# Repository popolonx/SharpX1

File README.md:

Sharp x1 related expansion boards
- CZ-8RS  RS232-serial board
- CZ-8RB One rom version (64K rom)
- CZ-VO-20PX with CPLD (vhd control board using CPLD for I/O logic)

Sharp teloper unit, CZ-8DT

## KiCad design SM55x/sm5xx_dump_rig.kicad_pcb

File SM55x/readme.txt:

SM550/1/2 (LU552xx used in Sharp VHD player) rom dump pcb with Raspberry PI pico

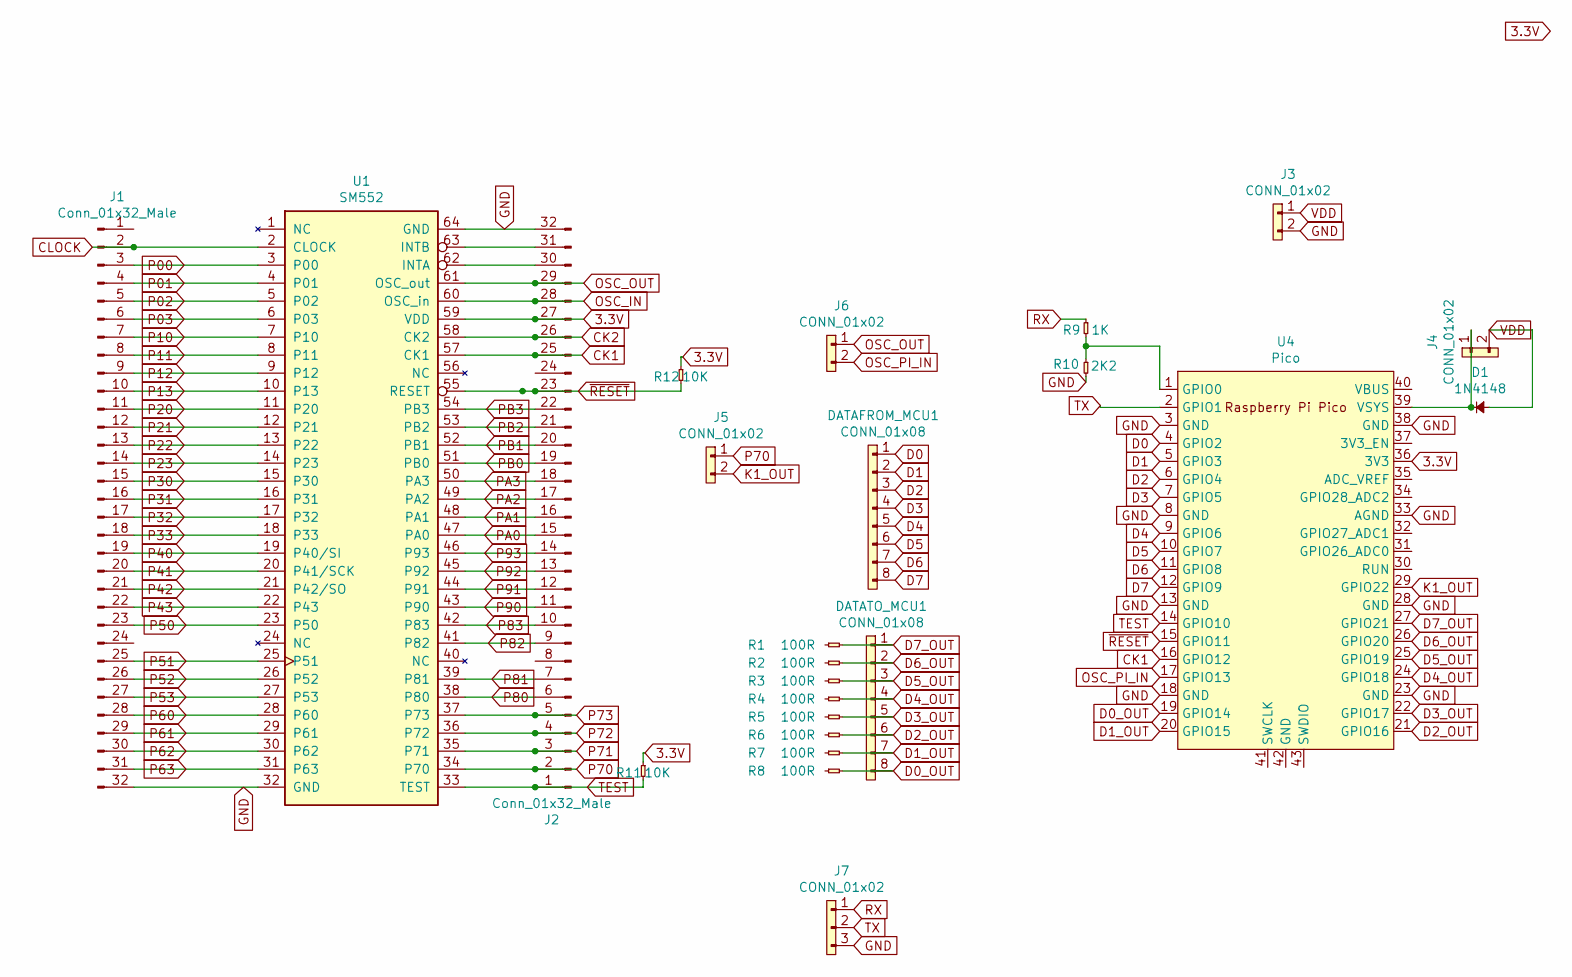
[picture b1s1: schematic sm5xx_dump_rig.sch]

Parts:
D1: 1N4148; D_DO-15_P5.08mm_Vertical_AnodeUp
DATAFROM_MCU1: CONN_01x08; PinHeader_1x08_P2.54mm_Vertical
DATATO_MCU1: CONN_01x08; PinHeader_1x08_P2.54mm_Vertical
J1, J2: Conn_01x32_Male; PinHeader_1x32_P2.54mm_Vertical
J3, J4, J5, J6: CONN_01x02; PinHeader_1x02_P2.54mm_Vertical
J7: CONN_01x02; PinHeader_1x03_P2.54mm_Vertical
R1, R2, R3, R4, R5, R6, R7, R8: 100R; R_Axial_DIN0204_L3.6mm_D1.6mm_P7.62mm_Horizontal
R9: 1K; R_Axial_DIN0204_L3.6mm_D1.6mm_P7.62mm_Horizontal
R10: 2K2; R_Axial_DIN0204_L3.6mm_D1.6mm_P7.62mm_Horizontal
R11, R12: 10K; R_Axial_DIN0204_L3.6mm_D1.6mm_P7.62mm_Horizontal
U1: SM552; DIP64_19.05mm_1.778mm
U4: Pico; RPi_Pico_THT

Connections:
3.3V: J2.27, R11.1, R12.1, U1.59 (VDD), U4.36 (3V3)
CK1: J2.25, U1.57 (CK1), U4.16 (GPIO12)
CK2: J2.26, U1.58 (CK2)
CLOCK: J1.2, U1.2 (CLOCK)
D0: DATAFROM_MCU1.1, U4.4 (GPIO2)
D0_OUT: DATATO_MCU1.8, R8.2, U4.19 (GPIO14)
D1: DATAFROM_MCU1.2, U4.5 (GPIO3)
D1_OUT: DATATO_MCU1.7, R7.2, U4.20 (GPIO15)
D2: DATAFROM_MCU1.3, U4.6 (GPIO4)
D2_OUT: DATATO_MCU1.6, R6.2, U4.21 (GPIO16)
D3: DATAFROM_MCU1.4, U4.7 (GPIO5)
D3_OUT: DATATO_MCU1.5, R5.2, U4.22 (GPIO17)
D4: DATAFROM_MCU1.5, U4.9 (GPIO6)
D4_OUT: DATATO_MCU1.4, R4.2, U4.24 (GPIO18)
D5: DATAFROM_MCU1.6, U4.10 (GPIO7)
D5_OUT: DATATO_MCU1.3, R3.2, U4.25 (GPIO19)
D6: DATAFROM_MCU1.7, U4.11 (GPIO8)
D6_OUT: DATATO_MCU1.2, R2.2, U4.26 (GPIO20)
D7: DATAFROM_MCU1.8, U4.12 (GPIO9)
D7_OUT: DATATO_MCU1.1, R1.2, U4.27 (GPIO21)
GND: J1.32, J2.32, J3.2, J7.3, R10.2, U1.32 (GND), U1.64 (GND), U4.3 (GND), U4.8 (GND), U4.13 (GND), U4.18 (GND), U4.23 (GND), U4.28 (GND), U4.33 (AGND), U4.38 (GND)
K1_OUT: J5.2, U4.29 (GPIO22)
unnamed: D1.1, J4.1, U4.39 (VSYS)
unnamed: J2.30, U1.62 (INTA)
unnamed: J2.31, U1.63 (INTB)
unnamed: R9.2, R10.1, U4.1 (GPIO0)
OSC_IN: J2.28, U1.60 (OSC_in)
OSC_OUT: J2.29, J6.1, U1.61 (OSC_out)
OSC_PI_IN: J6.2, U4.17 (GPIO13)
P00: J1.3, U1.3 (P00)
P01: J1.4, U1.4 (P01)
P02: J1.5, U1.5 (P02)
P03: J1.6, U1.6 (P03)
P10: J1.7, U1.7 (P10)
P11: J1.8, U1.8 (P11)
P12: J1.9, U1.9 (P12)
P13: J1.10, U1.10 (P13)
P20: J1.11, U1.11 (P20)
P21: J1.12, U1.12 (P21)
P22: J1.13, U1.13 (P22)
P23: J1.14, U1.14 (P23)
P30: J1.15, U1.15 (P30)
P31: J1.16, U1.16 (P31)
P32: J1.17, U1.17 (P32)
P33: J1.18, U1.18 (P33)
P40: J1.19, U1.19 (P40/SI)
P41: J1.20, U1.20 (P41/SCK)
P42: J1.21, U1.21 (P42/SO)
P43: J1.22, U1.22 (P43)
P50: J1.23, U1.23 (P50)
P51: J1.25, U1.25 (P51)
P52: J1.26, U1.26 (P52)
P53: J1.27, U1.27 (P53)
P60: J1.28, U1.28 (P60)
P61: J1.29, U1.29 (P61)
P62: J1.30, U1.30 (P62)
P63: J1.31, U1.31 (P63)
P70: J2.2, J5.1, U1.34 (P70)
P71: J2.3, U1.35 (P71)
P72: J2.4, U1.36 (P72)
P73: J2.5, U1.37 (P73)
P80: J2.6, U1.38 (P80)
P81: J2.7, U1.39 (P81)
P82: J2.9, U1.41 (P82)
P83: J2.10, U1.42 (P83)
P90: J2.11, U1.43 (P90)
P91: J2.12, U1.44 (P91)
P92: J2.13, U1.45 (P92)
P93: J2.14, U1.46 (P93)
PA0: J2.15, U1.47 (PA0)
PA1: J2.16, U1.48 (PA1)
PA2: J2.17, U1.49 (PA2)
PA3: J2.18, U1.50 (PA3)
PB0: J2.19, U1.51 (PB0)
PB1: J2.20, U1.52 (PB1)
PB2: J2.21, U1.53 (PB2)
PB3: J2.22, U1.54 (PB3)
RX: J7.1, R9.1
TEST: J2.1, R11.2, U1.33 (TEST), U4.14 (GPIO10)
TX: J7.2, U4.2 (GPIO1)
VDD: D1.2, J3.1, J4.2
~RESET~: J2.23, R12.2, U1.55 (RESET), U4.15 (GPIO11)

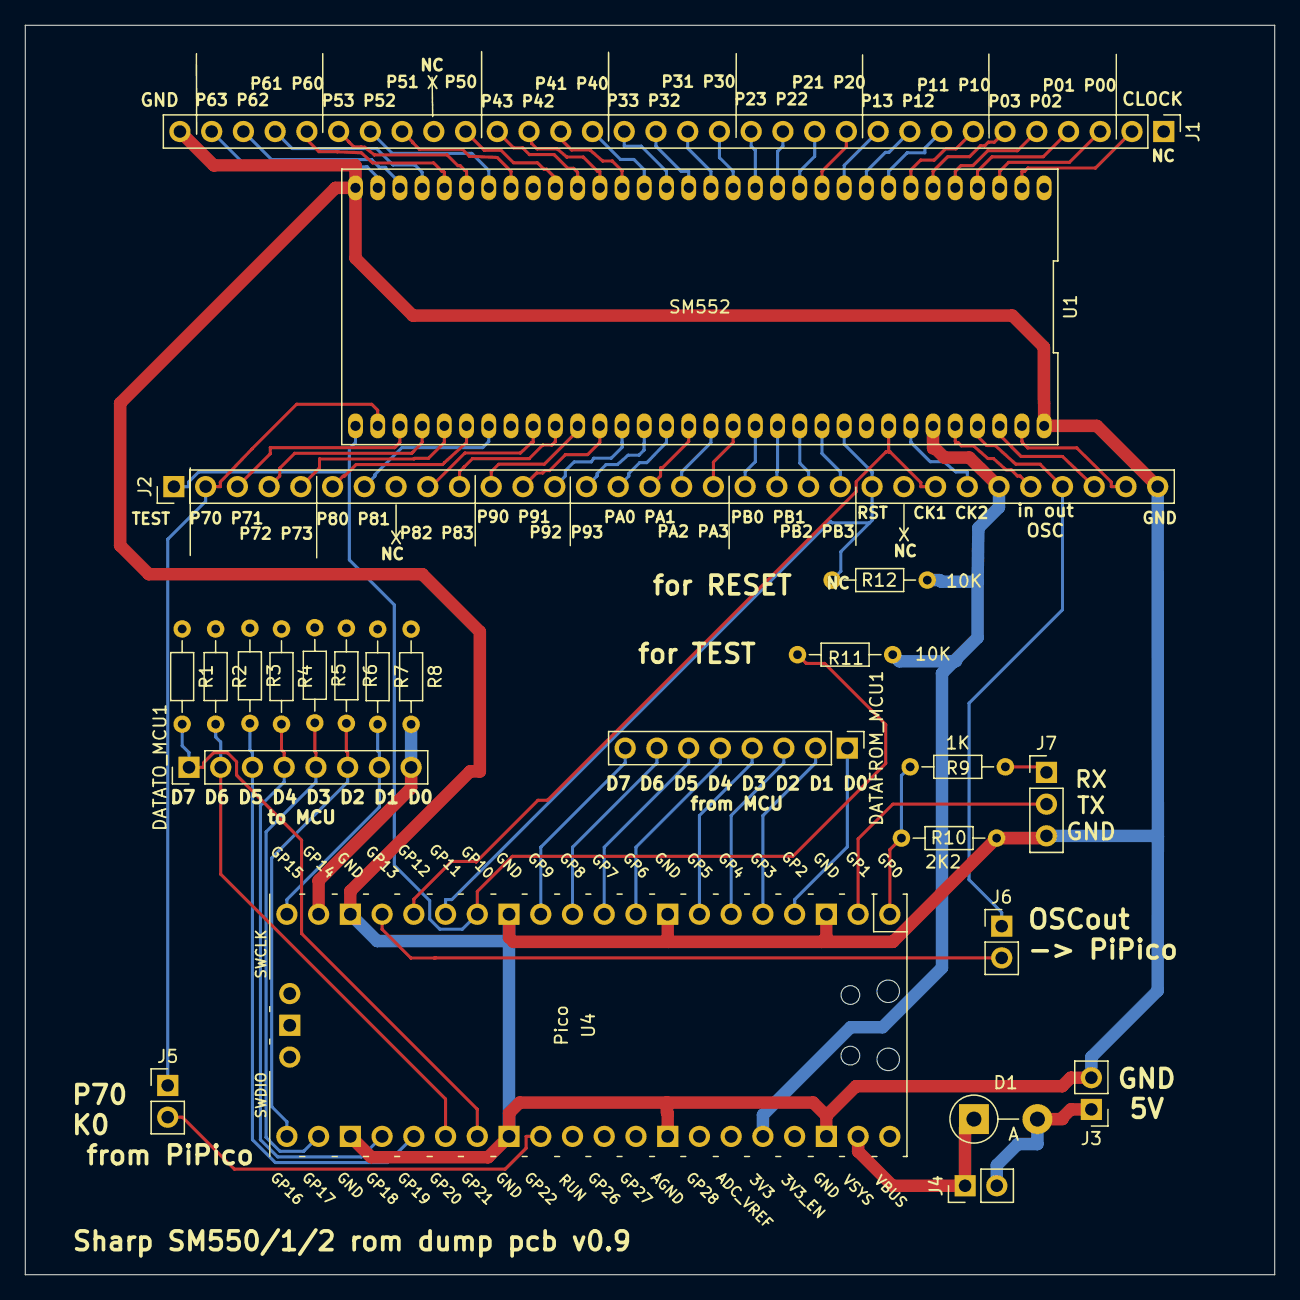
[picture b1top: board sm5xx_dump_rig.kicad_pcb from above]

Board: 2 copper layers, 100.0 x 100.0 mm, 24 parts (0 on the bottom side), 82 nets.

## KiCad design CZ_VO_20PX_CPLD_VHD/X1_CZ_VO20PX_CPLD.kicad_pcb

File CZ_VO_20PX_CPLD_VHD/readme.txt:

Sharp X1 vhd card
-implements vhd player control (VO-20PS + VO-20PC) and data decoding
-based on CZ-8RS card (RS-232) and msx vhd board (IF-C9C/D)
-CPLD version for logic side to decrease used ICs and pin count.
-DB15 connector towards VHD player (towards victor VHDpc din13, not for Sharp vhd din-8)
-needed cable connections:
--DIN13-pin3 <-> DB15-pin3
--DIN13-pin4 <-> DB15-pin4
--DIN13-pin6 <-> DB15-pin6
--DIN13-pin7 <-> DB15-pin7
--DIN13-pin8 <-> DB15-pin8
--DIN13-pin8 <-> DB15-pin9
--DIN13-pin10 <-> DB15-pin10
--DIN13-pin12 <-> DB15-pin12
--DIN13-shield <-> DB15-shield (is GND)

NOTE! Old kicad 5.1.5 used!

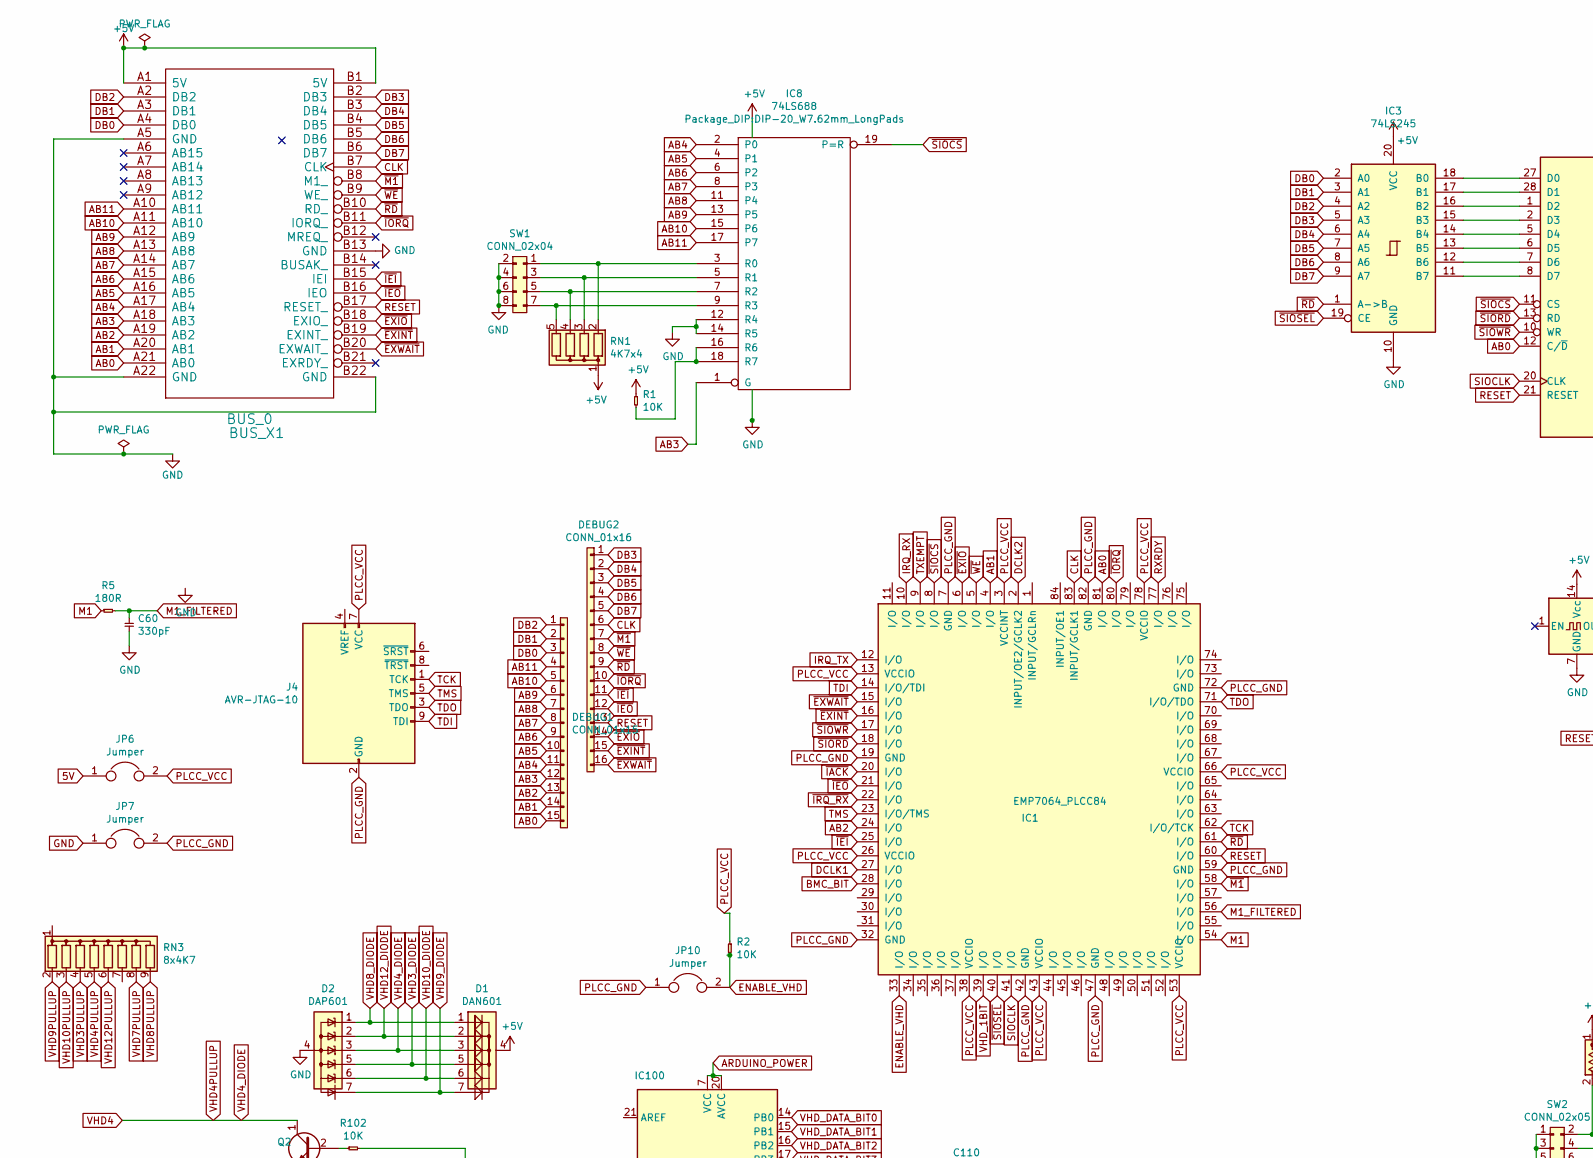
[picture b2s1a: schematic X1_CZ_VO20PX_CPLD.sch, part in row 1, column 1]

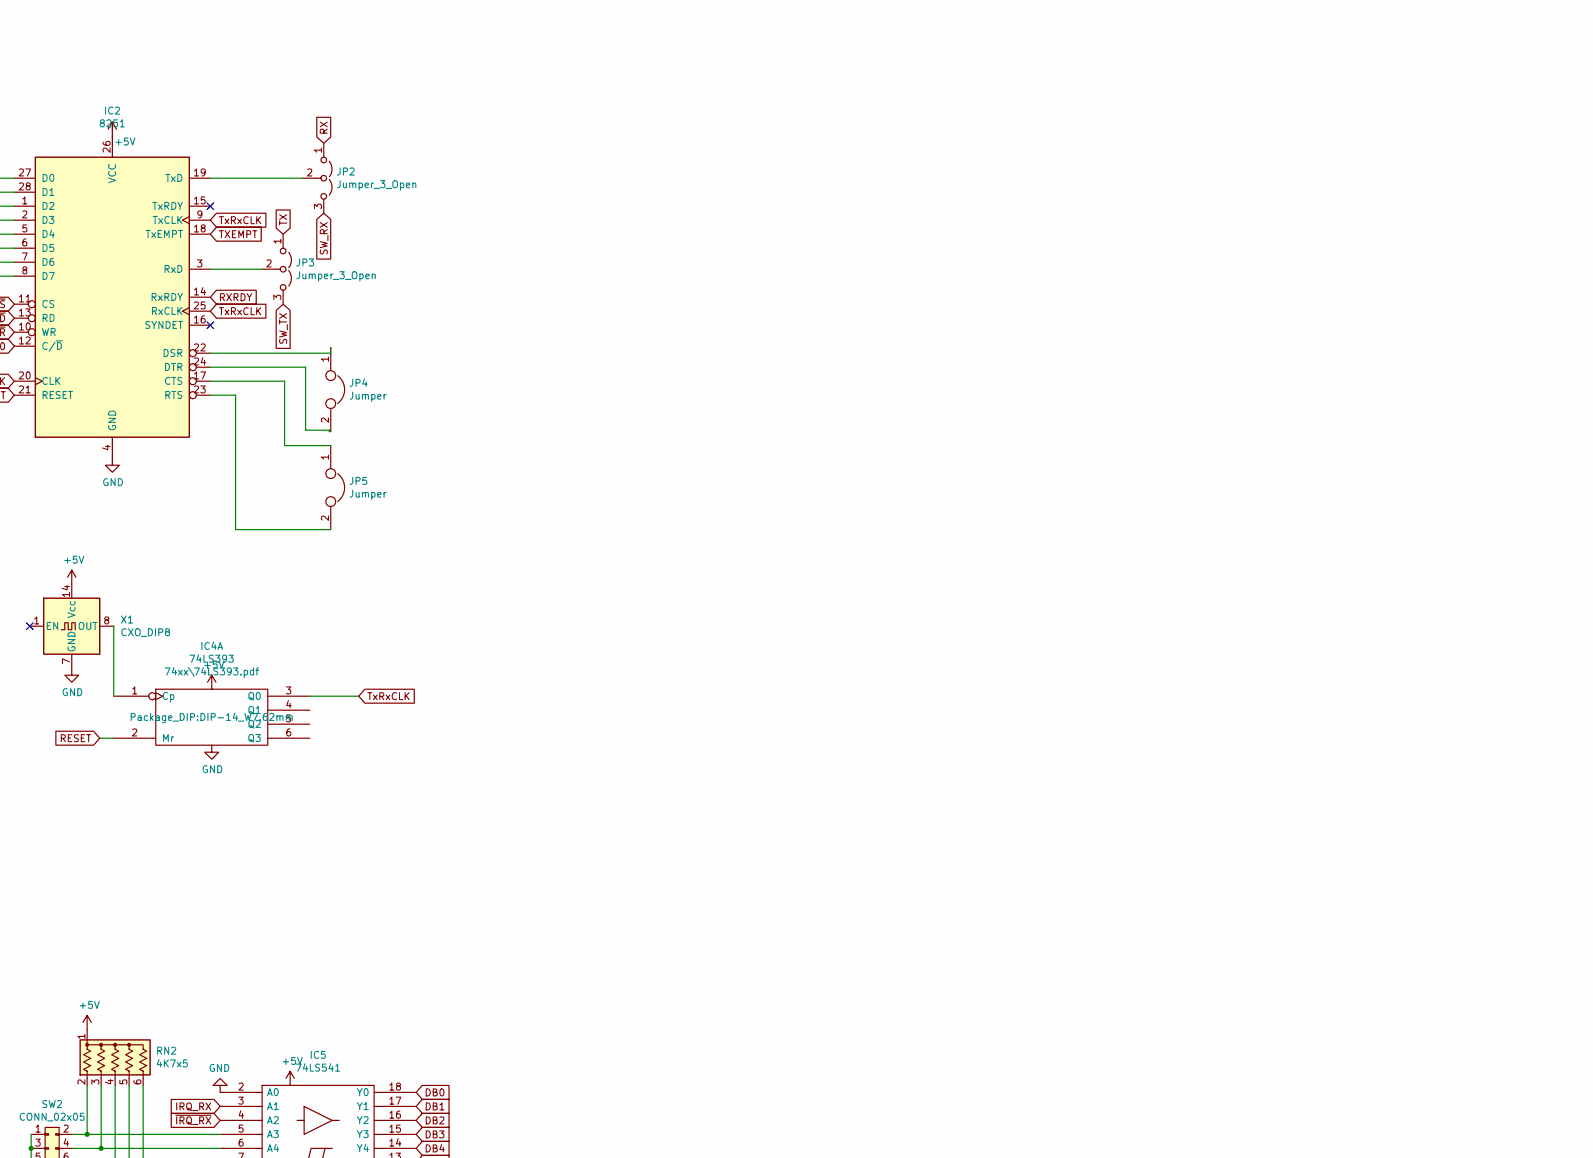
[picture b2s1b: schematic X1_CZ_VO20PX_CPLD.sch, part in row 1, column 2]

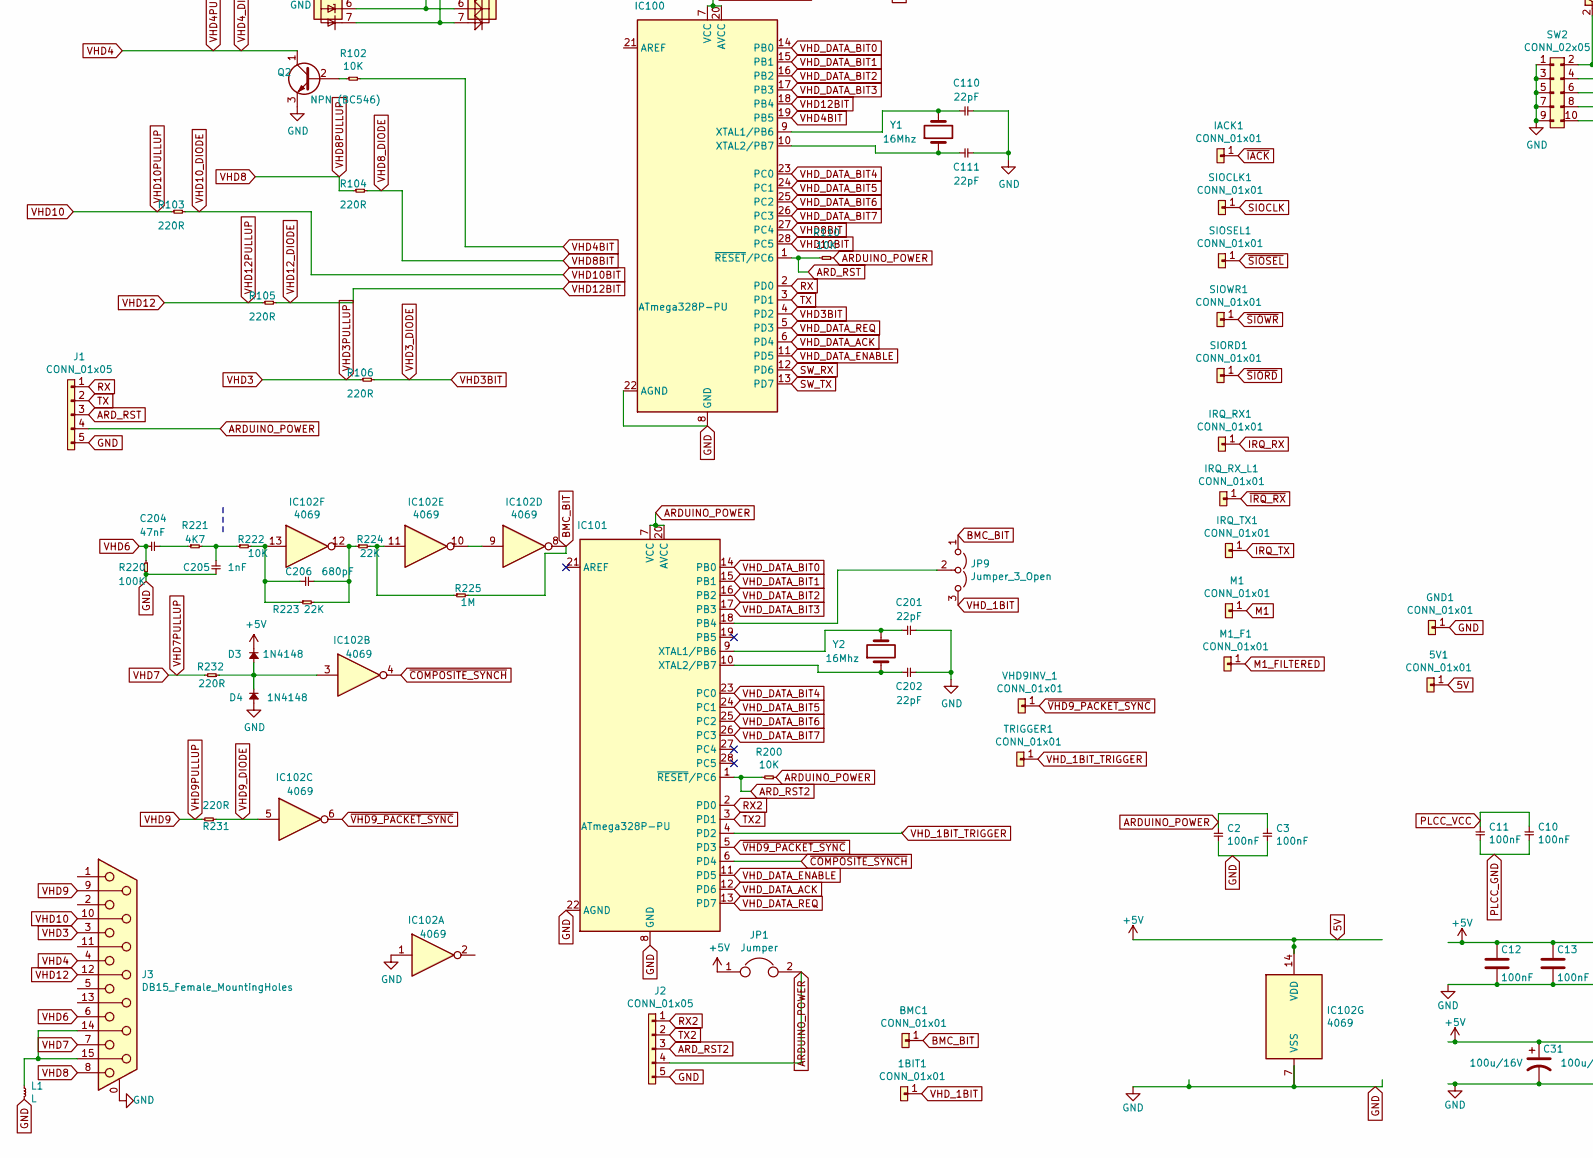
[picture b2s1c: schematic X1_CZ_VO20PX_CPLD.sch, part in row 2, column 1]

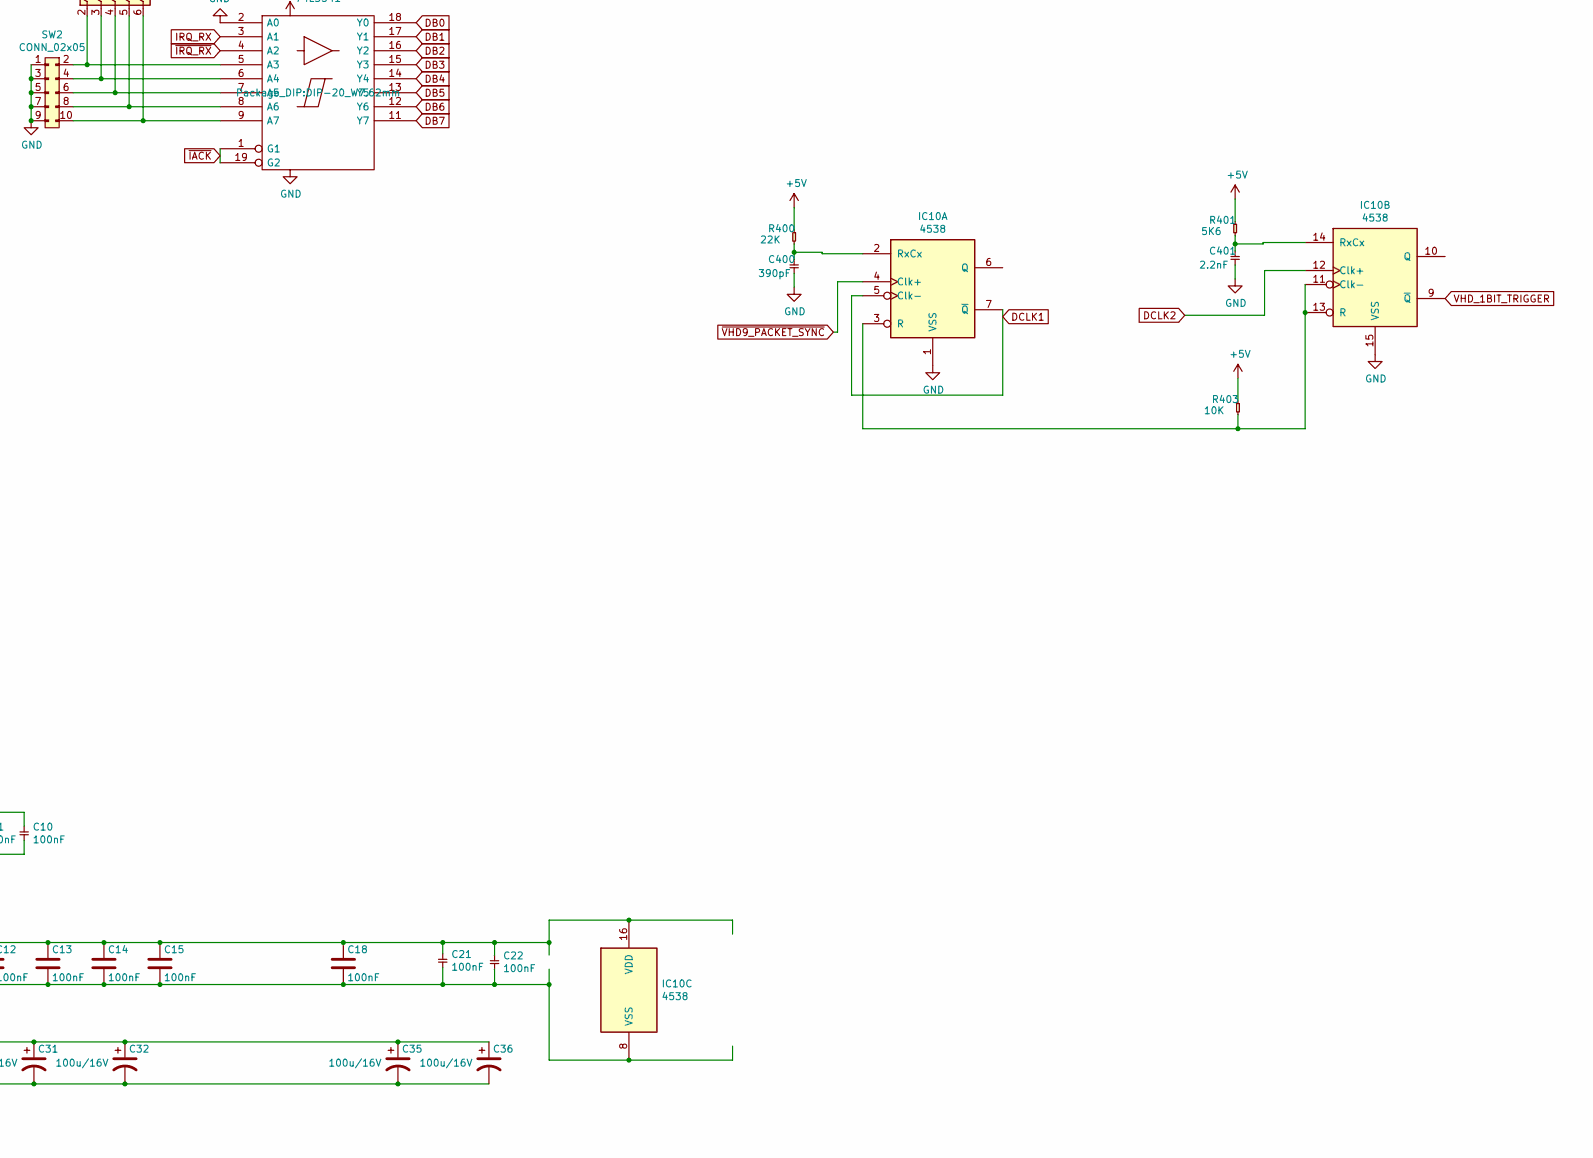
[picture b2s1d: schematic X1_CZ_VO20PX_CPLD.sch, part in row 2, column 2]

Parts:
1BIT1, 5V1: CONN_01x01; PinHeader_1x01_P2.54mm_Vertical
BMC1: CONN_01x01; PinHeader_1x01_P2.54mm_Vertical
BUS_0: BUS_X1; X1_IO
C2, C3, C10, C11, C12, C13, C14, C15, C18, C21, C22: 100nF; C_Disc_D5.0mm_W2.5mm_P5.00mm
C31, C32, C35: 100u/16V; CP_Radial_D8.0mm_P5.00mm
C36: 100u/16V; CP_Radial_D7.5mm_P2.50mm
C60: 330pF; C_Disc_D5.0mm_W2.5mm_P5.00mm
C110, C111, C201, C202: 22pF; C_Disc_D4.3mm_W1.9mm_P5.00mm
C204: 47nF; C_Disc_D5.0mm_W2.5mm_P5.00mm
C205: 1nF; C_Disc_D5.0mm_W2.5mm_P5.00mm
C206: 680pF; C_Disc_D5.0mm_W2.5mm_P5.00mm
C400: 390pF; C_Disc_D5.0mm_W2.5mm_P5.00mm
C401: 2.2nF; C_Disc_D5.0mm_W2.5mm_P5.00mm
D1: DAN601; R_Array_SIP7
D2: DAP601; R_Array_SIP7
D3, D4: 1N4148; D_A-405_P7.62mm_Horizontal
DEBUG1: CONN_01x15; PinHeader_1x15_P2.54mm_Vertical
DEBUG2: CONN_01x16; PinHeader_1x16_P2.54mm_Vertical
GND1: CONN_01x01; PinHeader_1x01_P2.54mm_Vertical
IACK1: CONN_01x01; PinHeader_1x01_P2.54mm_Vertical
IC1: EMP7064_PLCC84; PLCC-84_THT-Socket
IC2: 8251; DIP-28_W15.24mm
IC3: 74LS245; DIP-20_W7.62mm
IC4: 74LS393; DIP-14_W7.62mm
IC5: 74LS541; DIP-20_W7.62mm
IC8: 74LS688; DIP-20_W7.62mm_LongPads
IC10: 4538; DIP-16_W7.62mm_Socket_LongPads
IC100, IC101: ATmega328P-PU; DIP-28_W7.62mm
IC102: 4069; DIP-14_W7.62mm
IRQ_RX1: CONN_01x01; PinHeader_1x01_P2.54mm_Vertical
IRQ_RX_L1: CONN_01x01; PinHeader_1x01_P2.54mm_Vertical
IRQ_TX1: CONN_01x01; PinHeader_1x01_P2.54mm_Vertical
J1, J2: CONN_01x05; PinHeader_1x05_P2.54mm_Vertical
J3: DB15_Female_MountingHoles; DSUB-15_Female_Horizontal_P2.77x2.84mm_EdgePinOffset7.70mm_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
J4: AVR-JTAG-10; PinHeader_2x05_P2.54mm_Vertical
JP1, JP4, JP5, JP6, JP7, JP10: Jumper; PinHeader_1x02_P2.54mm_Vertical
JP2, JP3, JP9: Jumper_3_Open; PinHeader_1x03_P2.54mm_Vertical
L1: L; L_Axial_L5.3mm_D2.2mm_P10.16mm_Horizontal_Vishay_IM-1
M1, M1_F1: CONN_01x01; PinHeader_1x01_P2.54mm_Vertical
Q2: NPN (BC546); TO-92S_own
R1: 10K; R_Axial_DIN0309_L9.0mm_D3.2mm_P12.70mm_Horizontal
R2, R110: 10K; R_Axial_DIN0207_L6.3mm_D2.5mm_P7.62mm_Horizontal
R5: 180R; R_Axial_DIN0207_L6.3mm_D2.5mm_P7.62mm_Horizontal
R102, R222, R403: 10K; R_Axial_DIN0204_L3.6mm_D1.6mm_P7.62mm_Horizontal
R103, R104, R105, R106, R231, R232: 220R; R_Axial_DIN0204_L3.6mm_D1.6mm_P7.62mm_Horizontal
R200: 10K; R_Axial_DIN0207_L6.3mm_D2.5mm_P10.16mm_Horizontal
R220: 100K; R_Axial_DIN0204_L3.6mm_D1.6mm_P7.62mm_Horizontal
R221: 4K7; R_Axial_DIN0204_L3.6mm_D1.6mm_P7.62mm_Horizontal
R223, R224, R400: 22K; R_Axial_DIN0204_L3.6mm_D1.6mm_P7.62mm_Horizontal
R225: 1M; R_Axial_DIN0204_L3.6mm_D1.6mm_P7.62mm_Horizontal
R401: 5K6; R_Axial_DIN0204_L3.6mm_D1.6mm_P7.62mm_Horizontal
RN1: 4K7x4; R_Array_SIP5
RN2: 4K7x5; R_Array_SIP6
RN3: 8x4K7; R_Array_SIP9
SIOCLK1: CONN_01x01; PinHeader_1x01_P2.54mm_Vertical
SIORD1: CONN_01x01; PinHeader_1x01_P2.54mm_Vertical
SIOSEL1: CONN_01x01; PinHeader_1x01_P2.54mm_Vertical
SIOWR1: CONN_01x01; PinHeader_1x01_P2.54mm_Vertical
SW1: CONN_02x04; PinHeader_2x04_P2.54mm_Vertical
SW2: CONN_02x05; PinHeader_2x05_P2.54mm_Vertical
TRIGGER1: CONN_01x01; PinHeader_1x01_P2.54mm_Vertical
VHD9INV_1: CONN_01x01; PinHeader_1x01_P2.54mm_Vertical
X1: CXO_DIP8; Oscillator_DIP-14
Y1, Y2: 16Mhz; Crystal_HC18-U_Vertical

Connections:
5V: 5V1.1, BUS_0.A1 (5V), BUS_0.B1 (5V), C12.1, C13.1, C14.1, C15.1, C18.1, C21.1, C22.1, C31.1, C32.1, C35.1, C36.1, D1.4 (A), D3.1, IC2.26 (VCC), IC3.20 (VCC), IC4.14 (VCC), IC5.20 (VCC), IC8.20 (VCC), IC10.16 (VDD), IC102.14 (VDD), JP1.1, JP6.1, R1.1, R400.1, R401.1, R403.1, RN1.1 (common), RN2.1 (common), X1.14 (Vcc)
AB0: BUS_0.A21 (AB0), DEBUG1.15, IC1.81 (I/O), IC2.12 (C/~D)
AB1: BUS_0.A20 (AB1), DEBUG1.14, IC1.4 (I/O)
AB2: BUS_0.A19 (AB2), DEBUG1.13, IC1.24 (I/O)
AB3: BUS_0.A18 (AB3), DEBUG1.12, IC8.1 (G)
AB4: BUS_0.A17 (AB4), DEBUG1.11, IC8.2 (P0)
AB5: BUS_0.A16 (AB5), DEBUG1.10, IC8.4 (P1)
AB6: BUS_0.A15 (AB6), DEBUG1.9, IC8.6 (P2)
AB7: BUS_0.A14 (AB7), DEBUG1.8, IC8.8 (P3)
AB8: BUS_0.A13 (AB8), DEBUG1.7, IC8.11 (P4)
AB9: BUS_0.A12 (AB9), DEBUG1.6, IC8.13 (P5)
AB10: BUS_0.A11 (AB10), DEBUG1.5, IC8.15 (P6)
AB11: BUS_0.A10 (AB11), DEBUG1.4, IC8.17 (P7)
ARDUINO_POWER: C2.1, C3.1, IC100.7 (VCC), IC100.20 (AVCC), IC101.7 (VCC), IC101.20 (AVCC), J1.4, J2.4, JP1.2, R110.1, R200.1
ARD_RST: IC100.1 (~RESET~/PC6), J1.3, R110.2
ARD_RST2: IC101.1 (~RESET~/PC6), J2.3, R200.2
BMC_BIT: BMC1.1, IC1.28 (I/O), IC102.8, JP9.1 (A), R225.2
CLK: BUS_0.B7 (CLK), DEBUG2.6, IC1.83 (INPUT/GCLK1)
DB0: BUS_0.A4 (DB0), DEBUG1.3, IC3.2 (A0), IC5.18 (Y0)
DB1: BUS_0.A3 (DB1), DEBUG1.2, IC3.3 (A1), IC5.17 (Y1)
DB2: BUS_0.A2 (DB2), DEBUG1.1, IC3.4 (A2), IC5.16 (Y2)
DB3: BUS_0.B2 (DB3), DEBUG2.1, IC3.5 (A3), IC5.15 (Y3)
DB4: BUS_0.B3 (DB4), DEBUG2.2, IC3.6 (A4), IC5.14 (Y4)
DB5: BUS_0.B4 (DB5), DEBUG2.3, IC3.7 (A5), IC5.13 (Y5)
DB6: BUS_0.B5 (DB6), DEBUG2.4, IC3.8 (A6), IC5.12 (Y6)
DB7: BUS_0.B6 (DB7), DEBUG2.5, IC3.9 (A7), IC5.11 (Y7)
DCLK1: IC1.27 (I/O), IC10.5 (Clk-), IC10.7 (~Q)
DCLK2: IC1.2 (INPUT/OE2/GCLK2), IC10.12 (Clk+)
ENABLE_VHD: IC1.33 (I/O), JP10.2, R2.2
GND: BUS_0.A5 (GND), BUS_0.A22 (GND), BUS_0.B13 (GND), BUS_0.B22 (GND), C2.2, C3.2, C12.2, C13.2, C14.2, C15.2, C18.2, C21.2, C22.2, C31.2, C32.2, C35.2, C36.2, C60.2, C110.2, C111.2, C201.2, C202.2, C205.2, C400.2, C401.2, D2.4 (A), D4.2, GND1.1, IC2.4 (GND), IC3.10 (GND), IC4.7 (GND), IC5.2 (A0), IC5.10 (GND), IC8.10 (GND), IC8.12 (R4), IC8.14 (R5), IC10.1 (VSS), IC10.8 (VSS), IC10.15 (VSS), IC100.8 (GND), IC100.22 (AGND), IC101.8 (GND), IC101.22 (AGND), IC102.1, IC102.7 (VSS), J1.5, J2.5, J3.0 (PAD), JP7.1, L1.2, Q2.3 (E), R220.2, SW1.2, SW1.4, SW1.6, SW1.8, SW2.1, SW2.3, SW2.5, SW2.7, SW2.9, X1.7 (GND)
IRQ_RX: IC1.10 (I/O), IC5.3 (A1), IRQ_RX1.1
IRQ_TX: IC1.12 (I/O), IRQ_TX1.1
M1: IC1.54 (I/O), M1.1, R5.1
M1_FILTERED: C60.1, IC1.56 (I/O), M1_F1.1, R5.2
unnamed: C110.1, IC100.9 (XTAL1/PB6), Y1.2
unnamed: C111.1, IC100.10 (XTAL2/PB7), Y1.1
unnamed: C201.1, IC101.9 (XTAL1/PB6), Y2.2
unnamed: C202.1, IC101.10 (XTAL2/PB7), Y2.1
unnamed: C204.2, R221.1
unnamed: C205.1, R221.2, R222.1
unnamed: C206.1, IC102.13, R222.2, R223.1
unnamed: C206.2, IC102.12, R223.2, R224.1
unnamed: C400.1, IC10.2 (RxCx), R400.2
unnamed: C401.1, IC10.14 (RxCx), R401.2
unnamed: D3.2, D4.1, IC102.3, R232.1
unnamed: IC2.1 (D2), IC3.16 (B2)
unnamed: IC2.2 (D3), IC3.15 (B3)
unnamed: IC2.3 (RxD), JP3.2 (C)
unnamed: IC2.5 (D4), IC3.14 (B4)
unnamed: IC2.6 (D5), IC3.13 (B5)
unnamed: IC2.7 (D6), IC3.12 (B6)
unnamed: IC2.8 (D7), IC3.11 (B7)
unnamed: IC2.17 (CTS), JP5.1
unnamed: IC2.19 (TxD), JP2.2 (C)
unnamed: IC2.22 (DSR), JP4.1
unnamed: IC2.23 (RTS), JP5.2
unnamed: IC2.24 (DTR), JP4.2
unnamed: IC2.27 (D0), IC3.18 (B0)
unnamed: IC2.28 (D1), IC3.17 (B1)
unnamed: IC4.1 (Cp), X1.8 (OUT)
unnamed: IC5.5 (A3), RN2.2 (R1), SW2.2
unnamed: IC5.6 (A4), RN2.3 (R2), SW2.4
unnamed: IC5.7 (A5), RN2.4 (R3), SW2.6
unnamed: IC5.8 (A6), RN2.5 (R4), SW2.8
unnamed: IC5.9 (A7), RN2.6 (R5), SW2.10
unnamed: IC8.3 (R0), RN1.2 (R1), SW1.1
unnamed: IC8.5 (R1), RN1.3 (R2), SW1.3
unnamed: IC8.7 (R2), RN1.4 (R3), SW1.5
unnamed: IC8.9 (R3), RN1.5 (R4), SW1.7
unnamed: IC8.16 (R6), IC8.18 (R7), R1.2
unnamed: IC10.3 (R), IC10.11 (Clk-), IC10.13 (R), R403.2
unnamed: IC101.18 (PB4), JP9.2 (C)
unnamed: IC102.9, IC102.10
unnamed: IC102.11, R224.2, R225.1
unnamed: J3.14, J3.15, L1.1
unnamed: Q2.2 (B), R102.1
PLCC_GND: C10.2, C11.2, IC1.7 (GND), IC1.19 (GND), IC1.32 (GND), IC1.42 (GND), IC1.47 (GND), IC1.59 (GND), IC1.72 (GND), IC1.82 (GND), J4.2 (GND), J4.10 (GND), JP7.2, JP10.1
PLCC_VCC: C10.1, C11.1, IC1.3 (VCCINT), IC1.13 (VCCIO), IC1.26 (VCCIO), IC1.38 (VCCIO), IC1.43 (VCCIO), IC1.53 (VCCIO), IC1.66 (VCCIO), IC1.78 (VCCIO), J4.7 (VCC), JP6.2, R2.1
RESET: BUS_0.B17 (RESET_), DEBUG2.13, IC1.60 (I/O), IC2.21 (RESET), IC4.2 (Mr)
RX: IC100.2 (PD0), J1.1, JP2.1 (A)
RX2: IC101.2 (PD0), J2.1
RXRDY: IC1.77 (I/O), IC2.14 (RxRDY)
SIOCLK: IC1.41 (I/O), IC2.20 (CLK), SIOCLK1.1
SW_RX: IC100.12 (PD6), JP2.3 (B)
SW_TX: IC100.13 (PD7), JP3.3 (B)
TCK: IC1.62 (I/O/TCK), J4.1 (TCK)
TDI: IC1.14 (I/O/TDI), J4.9 (TDI)
TDO: IC1.71 (I/O/TDO), J4.3 (TDO)
TMS: IC1.23 (I/O/TMS), J4.5 (TMS)
TX: IC100.3 (PD1), J1.2, JP3.1 (A)
TX2: IC101.3 (PD1), J2.2
TXEMPT: IC1.9 (I/O), IC2.18 (TxEMPT)
TxRxCLK: IC2.9 (TxCLK), IC2.25 (RxCLK), IC4.3 (Q0)
VHD3: J3.3, R106.1, RN3.4 (R3)
VHD3BIT: D1.5 (K), D2.5 (K), IC100.4 (PD2), R106.2
VHD4: D1.3 (K), D2.3 (K), J3.4, Q2.1 (C), RN3.5 (R4)
VHD4BIT: IC100.19 (PB5), R102.2
VHD6: C204.1, J3.6, R220.1
VHD7: J3.7, R232.2, RN3.8 (R7)
VHD8: J3.8, R104.1, RN3.9 (R8)
VHD8BIT: D1.1 (K), D2.1 (K), IC100.27 (PC4), R104.2
VHD9: J3.9, R231.2, RN3.2 (R1)
VHD9_DIODE: D1.7 (K), D2.7 (K), IC102.5, R231.1
VHD10: J3.10, R103.1, RN3.3 (R2)
VHD10BIT: D1.6 (K), D2.6 (K), IC100.28 (PC5), R103.2
VHD12: J3.12, R105.1, RN3.6 (R5)
VHD12BIT: D1.2 (K), D2.2 (K), IC100.18 (PB4), R105.2
VHD_1BIT: 1BIT1.1, IC1.39 (I/O), JP9.3 (B)
VHD_1BIT_TRIGGER: IC10.9 (~Q), IC101.4 (PD2), TRIGGER1.1
VHD_DATA_ACK: IC100.6 (PD4), IC101.12 (PD6)
VHD_DATA_BIT0: IC100.14 (PB0), IC101.14 (PB0)
VHD_DATA_BIT1: IC100.15 (PB1), IC101.15 (PB1)
VHD_DATA_BIT2: IC100.16 (PB2), IC101.16 (PB2)
VHD_DATA_BIT3: IC100.17 (PB3), IC101.17 (PB3)
VHD_DATA_BIT4: IC100.23 (PC0), IC101.23 (PC0)
VHD_DATA_BIT5: IC100.24 (PC1), IC101.24 (PC1)
VHD_DATA_BIT6: IC100.25 (PC2), IC101.25 (PC2)
VHD_DATA_BIT7: IC100.26 (PC3), IC101.26 (PC3)
VHD_DATA_ENABLE: IC100.11 (PD5), IC101.11 (PD5)
VHD_DATA_REQ: IC100.5 (PD3), IC101.13 (PD7)
~COMPOSITE_SYNCH: IC101.6 (PD4), IC102.4
~EXINT: BUS_0.B19 (EXINT_), DEBUG2.15, IC1.16 (I/O)
~EXIO: BUS_0.B18 (EXIO_), DEBUG2.14, IC1.6 (I/O)
~EXWAIT: BUS_0.B20 (EXWAIT_), DEBUG2.16, IC1.15 (I/O)
~IACK: IACK1.1, IC1.20 (I/O), IC5.1 (G1), IC5.19 (G2)
~IEI: BUS_0.B15 (IEI), DEBUG2.11, IC1.25 (I/O)
~IEO: BUS_0.B16 (IEO), DEBUG2.12, IC1.21 (I/O)
~IORQ: BUS_0.B11 (IORQ_), DEBUG2.10, IC1.80 (I/O)
~IRQ_RX: IC1.22 (I/O), IC5.4 (A2), IRQ_RX_L1.1
~M1: BUS_0.B8 (M1_), DEBUG2.7, IC1.58 (I/O)
~RD: BUS_0.B10 (RD_), DEBUG2.9, IC1.61 (I/O), IC3.1 (A->B)
~SIOCS: IC1.8 (I/O), IC2.11 (CS), IC8.19 (P=R)
~SIORD: IC1.18 (I/O), IC2.13 (RD), SIORD1.1
~SIOSEL: IC1.40 (I/O), IC3.19 (CE), SIOSEL1.1
~SIOWR: IC1.17 (I/O), IC2.10 (WR), SIOWR1.1
~VHD9_PACKET_SYNC: IC10.4 (Clk+), IC101.5 (PD3), IC102.6, VHD9INV_1.1
~WE: BUS_0.B9 (WE_), DEBUG2.8, IC1.5 (I/O)

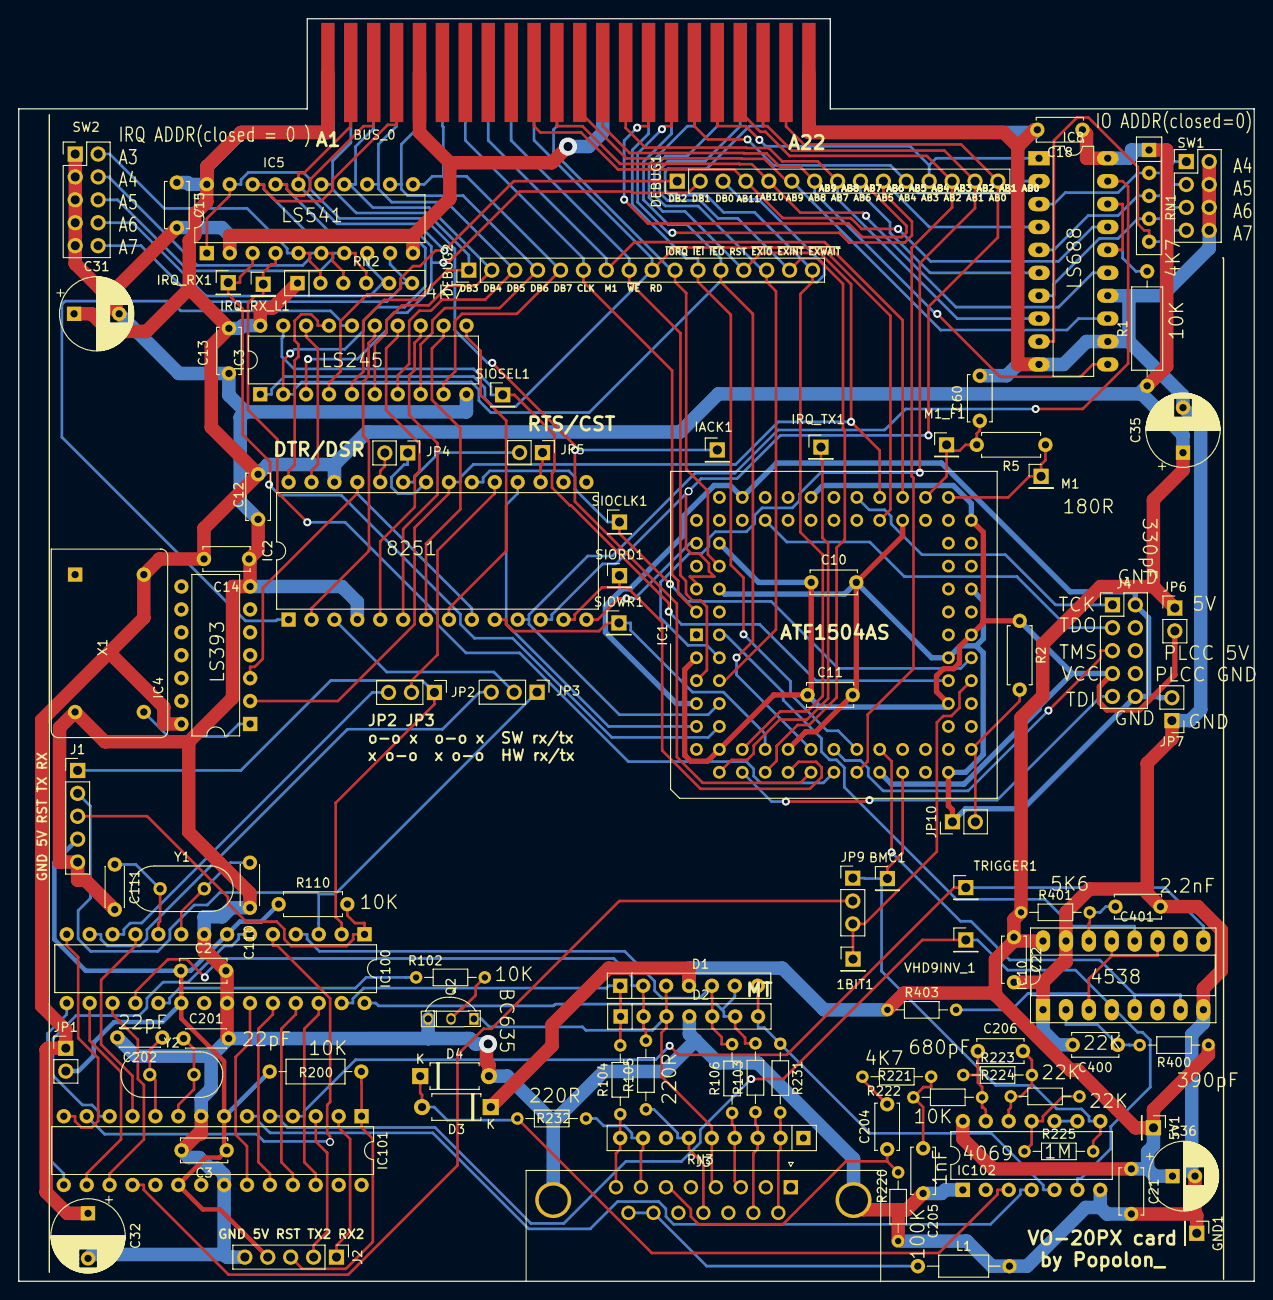
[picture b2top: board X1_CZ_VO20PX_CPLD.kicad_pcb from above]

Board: 2 copper layers, 137.0 x 140.0 mm, 102 parts (0 on the bottom side), 137 nets.
